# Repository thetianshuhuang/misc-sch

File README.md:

# misc-sch
Random eagle schematics, some of which have been fabricated, some that haven't, and some that probably will never get made.

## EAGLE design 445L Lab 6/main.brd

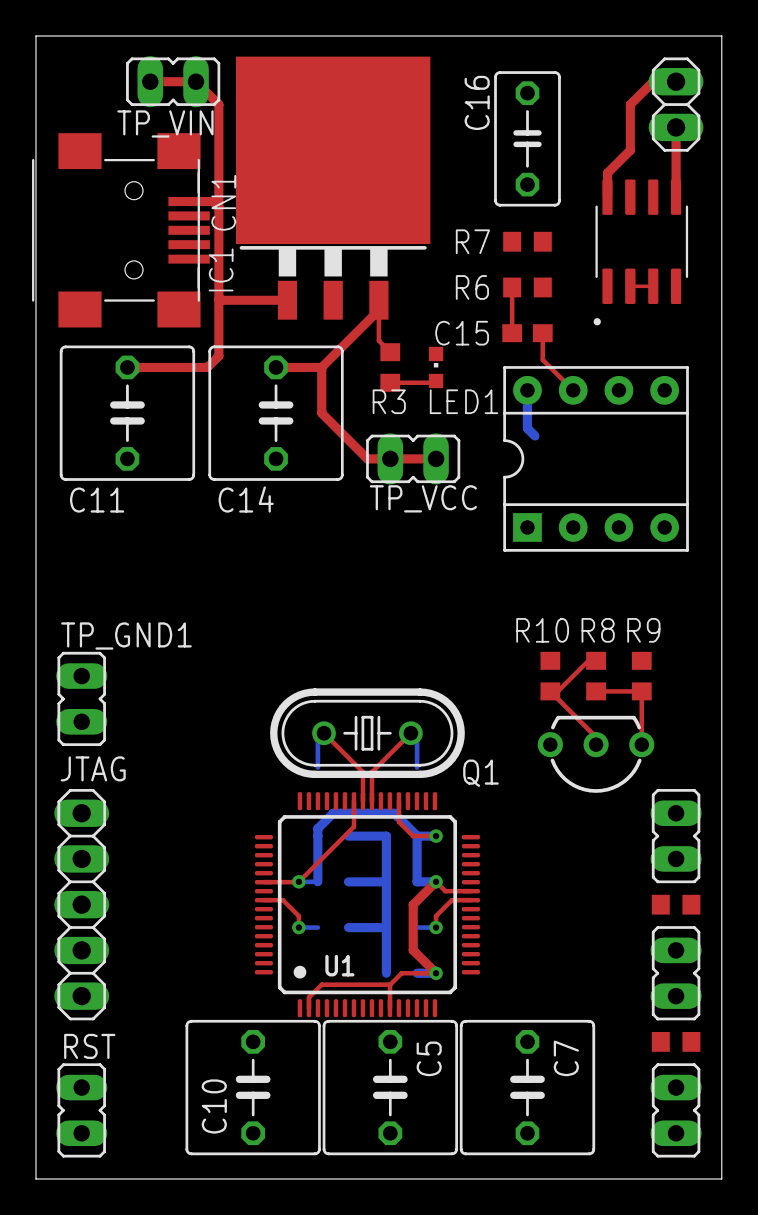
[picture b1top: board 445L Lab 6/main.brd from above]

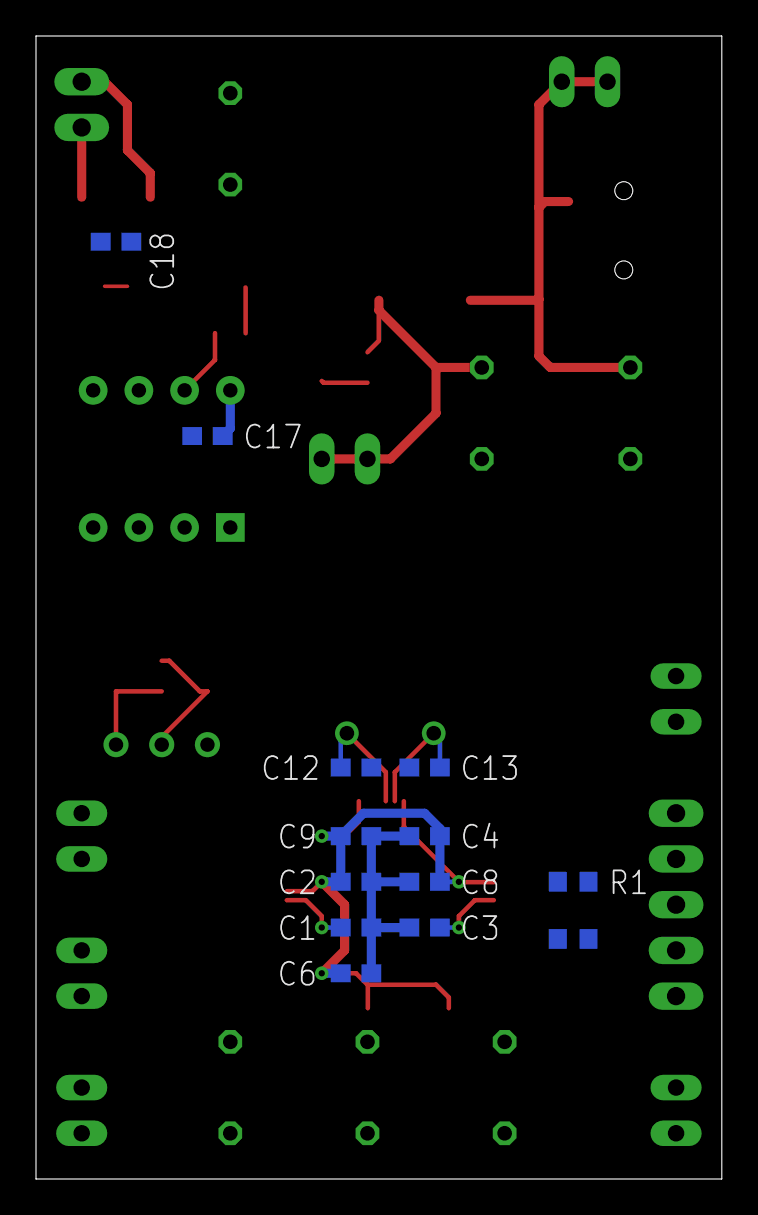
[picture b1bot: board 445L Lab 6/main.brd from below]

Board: 2 copper layers, 38.1 x 63.5 mm, 45 parts (13 on the bottom side), 26 nets.

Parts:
BTN0, BTN4: JP1
C1, C3, C8, C9, C15, C17, C18: 0.1uF; C0603
C2, C4, C6: 0.01uF; C0603
C5, C10: 1uF; C050-075X075
C7: 2.2uF; C050-075X075
C11, C14: 4.7uF; C050-075X075
C12, C13: 10pF; C0603
C16: 3.3uF; C050-035X075
CN1: USB-MINIB
IC1: LM2937; TO263-3
IC2: LM4041CILPRLP; LP_O-PBCY-W3
JTAG: 1X05
LED1: CHIPLED_0603
Q1: 16MHz; HC49U-V
R1: 1M; R0603
R2: 10K; R0603
R3: 4.7K; R0603
R4, R5, R9: 10k; R0603
R6, R7: 2.2k; R0603
R8: 47k; R0603
R10: 2k; R0603
RST: JP1
SPK: 1X02
TP_GND1, TP_GND2: JP1
TP_VCC: JP1
TP_VIN: JP1
U1: TM4C1233H6PM; LQFP64
U2: TPA731D; SOIC127P600X175-8N
U3: TLV5616; DIL08

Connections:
5V_IN: C11.1, CN1.VBUS, IC1.1, TP_VIN.1, TP_VIN.2
AMP_DC_FILTER: C15.2, R6.1
AMP_IN+: C16.1, U2.2, U2.3
AMP_IN-: R6.2, R7.1, U2.4
FSS: U1.20, U3.4
GND: BTN0.2, BTN4.2, C1.2, C2.2, C3.2, C4.2, C5.2, C6.2, C7.2, C8.2, C9.2, C10.2, C11.2, C12.2, C13.2, C14.2, C16.2, C17.2, C18.2, CN1.GND, IC1.2, IC2.3, JTAG.5, LED1.C, R9.2, RST.2, TP_GND1.1, TP_GND1.2, TP_GND2.1, TP_GND2.2, U1.3, U1.12, U1.27, U1.34, U1.35, U1.39, U1.55, U2.7, U3.3, U3.5
LED_RESIST: LED1.A, R3.1
MOSI: U1.22, U3.1
OSC0: C12.1, Q1.1, U1.40
OSC1: C13.1, Q1.2, U1.41
PF0: BTN0.1, R4.2, U1.28
PF4: BTN4.1, R5.2, U1.5
RST: R2.1, RST.1, U1.38
SCLK: U1.19, U3.2
TCK: JTAG.4, U1.52
TDI: JTAG.2, U1.50
TDO: JTAG.1, U1.49
TMS: JTAG.3, U1.51
VCC: C2.1, C4.1, C6.1, C8.1, C9.1, C10.1, C14.1, C17.1, C18.1, IC1.3, R1.2, R2.2, R3.2, R4.1, R5.1, R10.2, TP_VCC.1, TP_VCC.2, U1.2, U1.11, U1.26, U1.37, U1.42, U1.54, U2.6, U3.8
VDAC: C15.1, U3.7
VDDC: C1.1, C3.1, C5.1, C7.1, U1.25, U1.56
VO+: R7.2, SPK.1, U2.5
VO-: SPK.2, U2.8
VREF: IC2.2, R8.1, R10.1, U3.6
VREF_FEEDBACK: IC2.1, R8.2, R9.1
WAKE: R1.1, U1.32

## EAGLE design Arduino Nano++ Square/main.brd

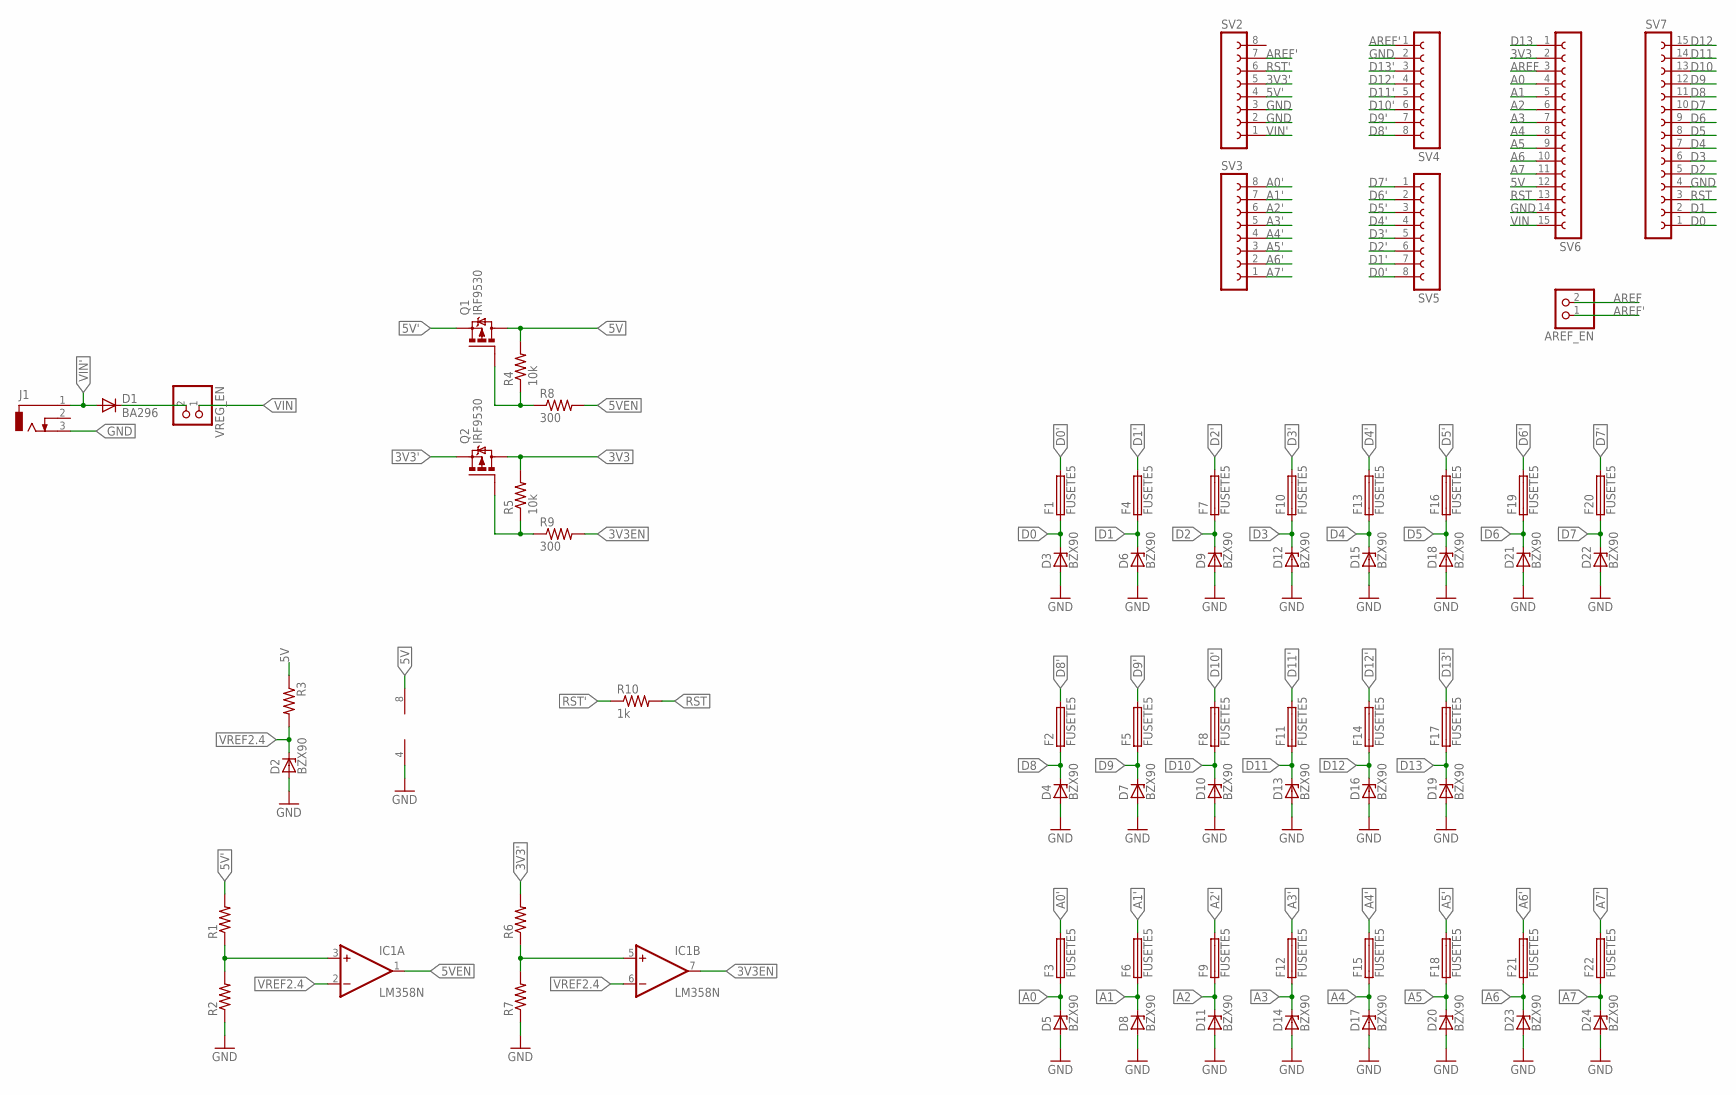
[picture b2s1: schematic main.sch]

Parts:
AREF_EN: PINHD-1X2; 1X02
D1: BA296; P2-15
D2, D3, D4, D5, D6, D7, D8, D9, D10, D11, D12, D13, D14, D15, D16, D17, D18, D19, D20, D21, D22, D23, D24: BZX90; DO34Z7
F1, F2, F3, F4, F5, F6, F7, F8, F9, F10, F11, F12, F13, F14, F15, F16, F17, F18, F19, F20, F21, F22: FUSETE5; TE5
IC1: LM358N; DIL08
J1: DCJ0303
Q1, Q2: IRF9530; TO220BV
R1, R2, R3, R6, R7: R-US_0204/7; 0204/7
R4, R5: 10k; 0204/7
R8, R9: 300; 0204/7
R10: 1k; 0204/7
SV2, SV3, SV4, SV5: FE08-1; FE08
SV6, SV7: FE15-1; FE15
VREG_EN: PINHD-1X2; 1X02

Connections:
3V3: Q2.D, R5.2, SV6.2
3V3': Q2.S, R6.2, SV2.5
3V3EN: IC1.7 (OUT), R9.2
5V: IC1.8 (V+), Q1.D, R3.1, R4.2, SV6.12
5V': Q1.S, R1.2, SV2.4
5VEN: IC1.1 (OUT), R8.2
A0: D5.C, F3.1, SV6.4
A0': F3.2, SV3.8
A1: D8.C, F6.1, SV6.5
A1': F6.2, SV3.7
A2: D11.C, F9.1, SV6.6
A2': F9.2, SV3.6
A3: D14.C, F12.1, SV6.7
A3': F12.2, SV3.5
A4: D17.C, F15.1, SV6.8
A4': F15.2, SV3.4
A5: D20.C, F18.1, SV6.9
A5': F18.2, SV3.3
A6: D23.C, F21.1, SV6.10
A6': F21.2, SV3.2
A7: D24.C, F22.1, SV6.11
A7': F22.2, SV3.1
AREF: AREF_EN.2, SV6.3
AREF': AREF_EN.1, SV2.7, SV4.1
D0: D3.C, F1.1, SV7.1
D0': F1.2, SV5.8
D1: D6.C, F4.1, SV7.2
D1': F4.2, SV5.7
D2: D9.C, F7.1, SV7.5
D2': F7.2, SV5.6
D3: D12.C, F10.1, SV7.6
D3': F10.2, SV5.5
D4: D15.C, F13.1, SV7.7
D4': F13.2, SV5.4
D5: D18.C, F16.1, SV7.8
D5': F16.2, SV5.3
D6: D21.C, F19.1, SV7.9
D6': F19.2, SV5.2
D7: D22.C, F20.1, SV7.10
D7': F20.2, SV5.1
D8: D4.C, F2.1, SV7.11
D8': F2.2, SV4.8
D9: D7.C, F5.1, SV7.12
D9': F5.2, SV4.7
D10: D10.C, F8.1, SV7.13
D10': F8.2, SV4.6
D11: D13.C, F11.1, SV7.14
D11': F11.2, SV4.5
D12: D16.C, F14.1, SV7.15
D12': F14.2, SV4.4
D13: D19.C, F17.1, SV6.1
D13': F17.2, SV4.3
GND: D2.A, D3.A, D4.A, D5.A, D6.A, D7.A, D8.A, D9.A, D10.A, D11.A, D12.A, D13.A, D14.A, D15.A, D16.A, D17.A, D18.A, D19.A, D20.A, D21.A, D22.A, D23.A, D24.A, IC1.4 (V-), J1.3, R2.1, R7.1, SV2.2, SV2.3, SV4.2, SV6.14, SV7.4
unnamed: D1.C, VREG_EN.2
unnamed: Q2.G, R5.1, R9.1
unnamed: Q1.G, R4.1, R8.1
unnamed: IC1.3 (+IN), R1.1, R2.2
unnamed: IC1.5 (+IN), R6.1, R7.2
RST: R10.2, SV6.13, SV7.3
RST': R10.1, SV2.6
VIN: SV6.15, VREG_EN.1
VIN': D1.A, J1.1, SV2.1
VREF2.4: D2.C, IC1.2 (-IN), IC1.6 (-IN), R3.2

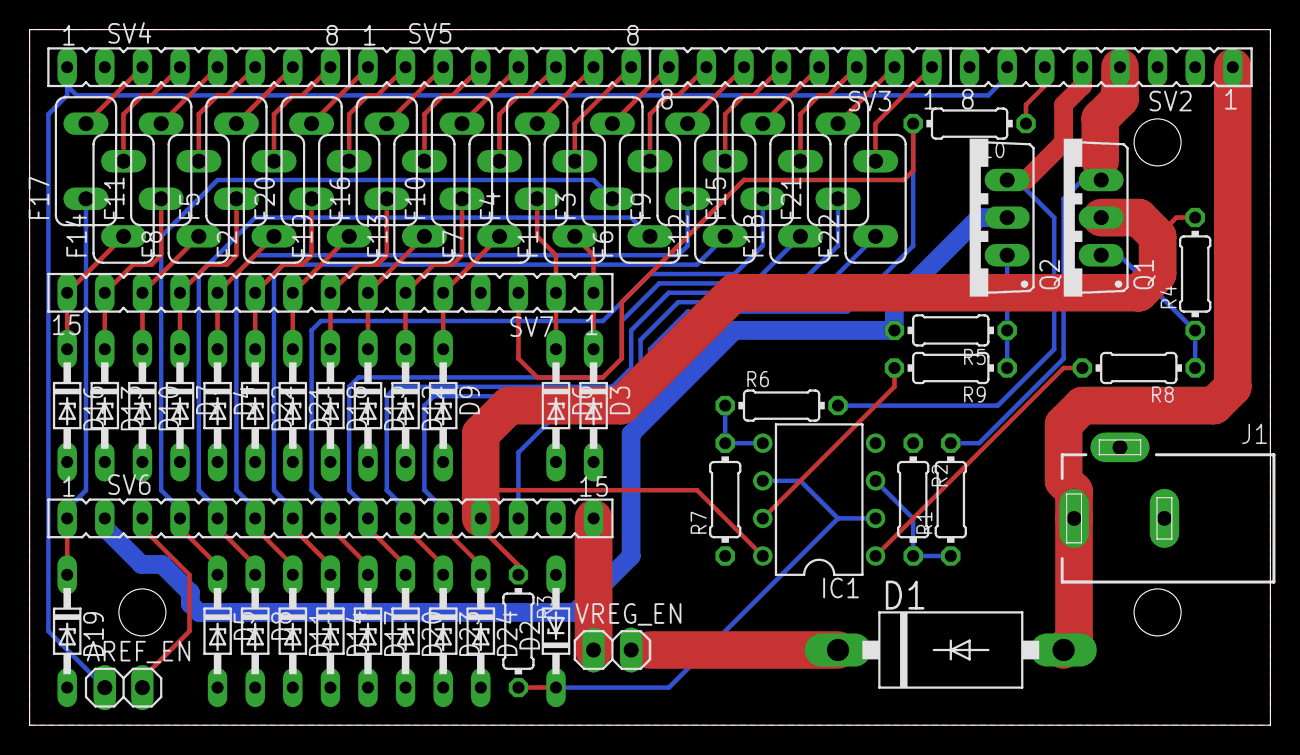
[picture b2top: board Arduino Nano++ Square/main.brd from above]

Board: 2 copper layers, 83.8 x 47.0 mm, 68 parts (0 on the bottom side), 63 nets.

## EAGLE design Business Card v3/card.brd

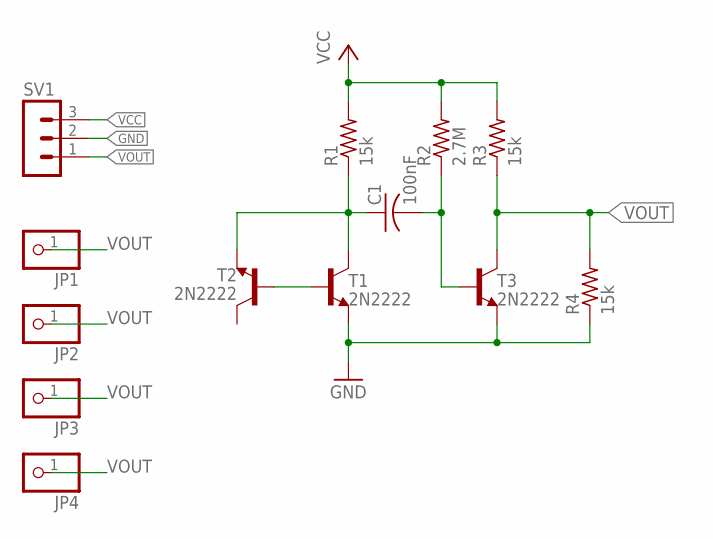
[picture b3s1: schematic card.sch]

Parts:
C1: 100nF; C025-025X050
JP1, JP2, JP3, JP4: PINHD-1X1; 1X01
R1, R3, R4: 15k; 0204/7
R2: 2.7M; 0204/7
SV1: MA03-1
T1, T2, T3: 2N2222; TO18

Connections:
GND: R4.1, SV1.2, T1.1 (E), T3.1 (E)
unnamed: T1.2 (B), T2.2 (B)
unnamed: C1.1, R1.1, T1.3 (C), T2.1 (E)
unnamed: C1.2, R2.1, T3.2 (B)
VCC: R1.2, R2.2, R3.2, SV1.3
VOUT: JP1.1, JP2.1, JP3.1, JP4.1, R3.1, R4.2, SV1.1, T3.3 (C)

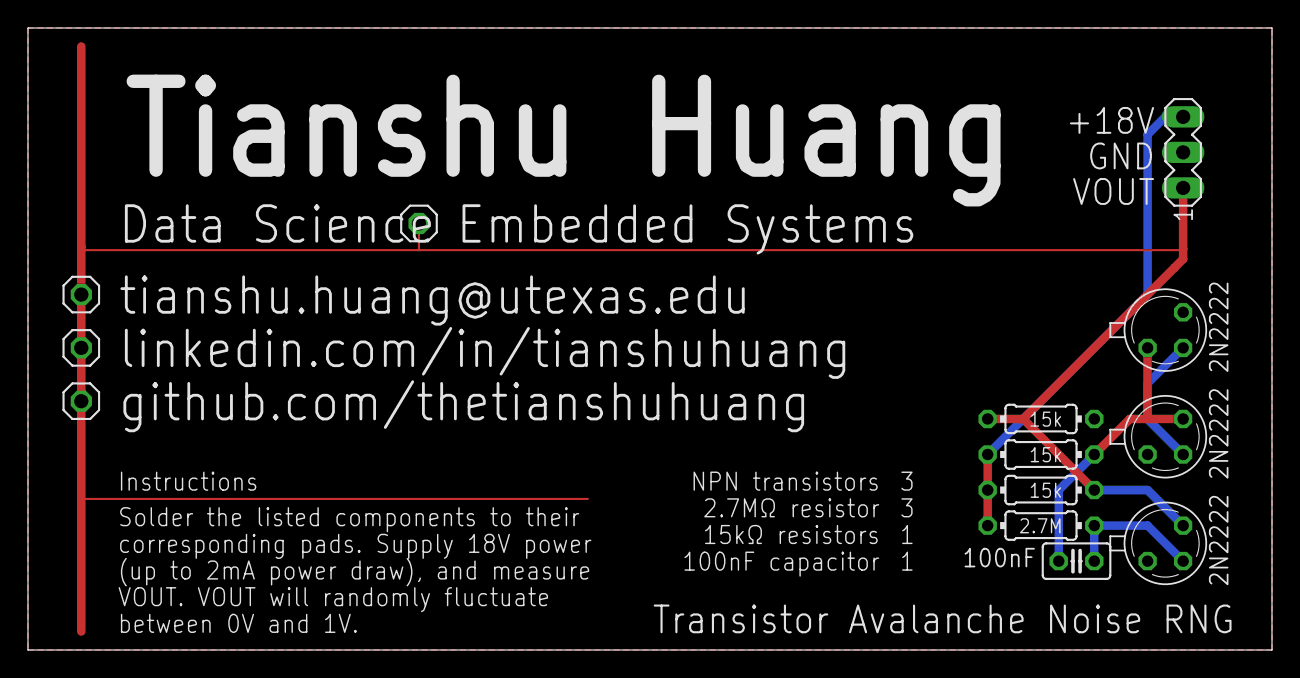
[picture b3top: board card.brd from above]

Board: 2 copper layers, 88.9 x 44.5 mm, 13 parts (0 on the bottom side), 6 nets.

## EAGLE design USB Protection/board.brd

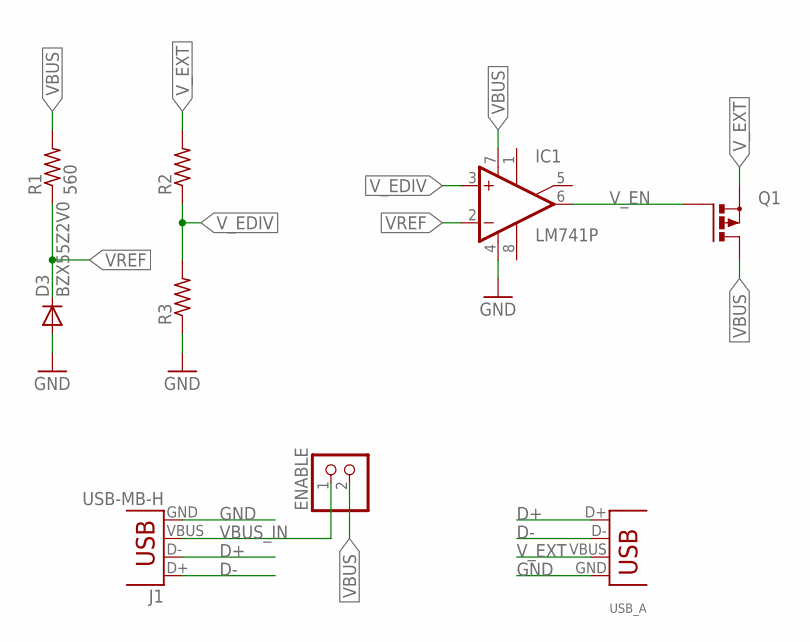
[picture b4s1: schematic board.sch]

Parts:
D3: BZX55Z2V0; DO35-7
ENABLE: PINHD-1X2; 1X02
IC1: LM741P; DIL08
J1: USB-MB-H
Q1: PMOSFET_PTO220BV; TO220BV
R1: 560; 0207/7
R2, R3: R-US_0207/7; 0207/7
USB_A: USB-A-H

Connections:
D+: J1.D-, USB_A.D+
D-: J1.D+, USB_A.D-
GND: D3.A, IC1.4 (V-), J1.GND, R3.1, USB_A.GND
VBUS: ENABLE.2, IC1.7 (V+), Q1.D, R1.2
VBUS_IN: ENABLE.1, J1.VBUS
VREF: D3.C, IC1.2 (-IN), R1.1
V_EDIV: IC1.3 (+IN), R2.1, R3.2
V_EN: IC1.6 (OUT), Q1.G
V_EXT: Q1.S, R2.2, USB_A.VBUS

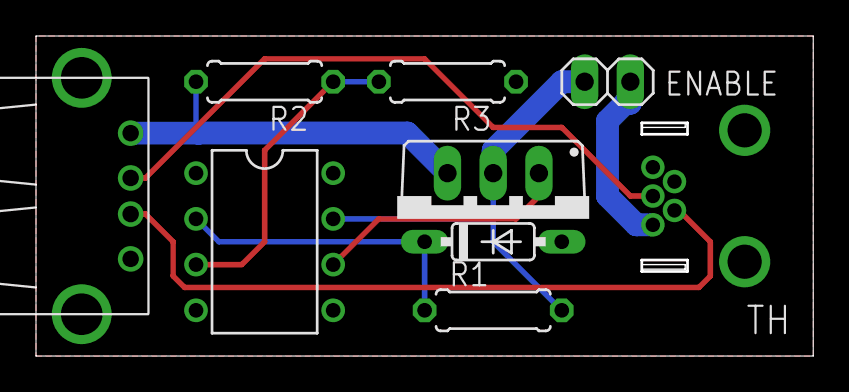
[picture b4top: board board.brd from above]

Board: 2 copper layers, 43.0 x 17.6 mm, 9 parts (0 on the bottom side), 9 nets.

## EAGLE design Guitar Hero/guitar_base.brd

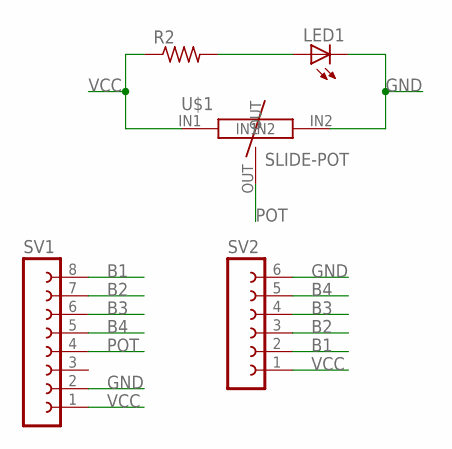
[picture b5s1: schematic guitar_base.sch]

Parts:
LED1: LED5MM
R2: R-US_0207/7; 0207/7
SV1: FE08-1; FE08
SV2: FE06-1; FE06
U$1: SLIDE-POT

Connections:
B1: SV1.8, SV2.2
B2: SV1.7, SV2.3
B3: SV1.6, SV2.4
B4: SV1.5, SV2.5
GND: LED1.K (C), SV1.2, SV2.6, U$1.IN2
unnamed: LED1.A, R2.2
POT: SV1.4, U$1.OUT
VCC: R2.1, SV1.1, SV2.1, U$1.IN1

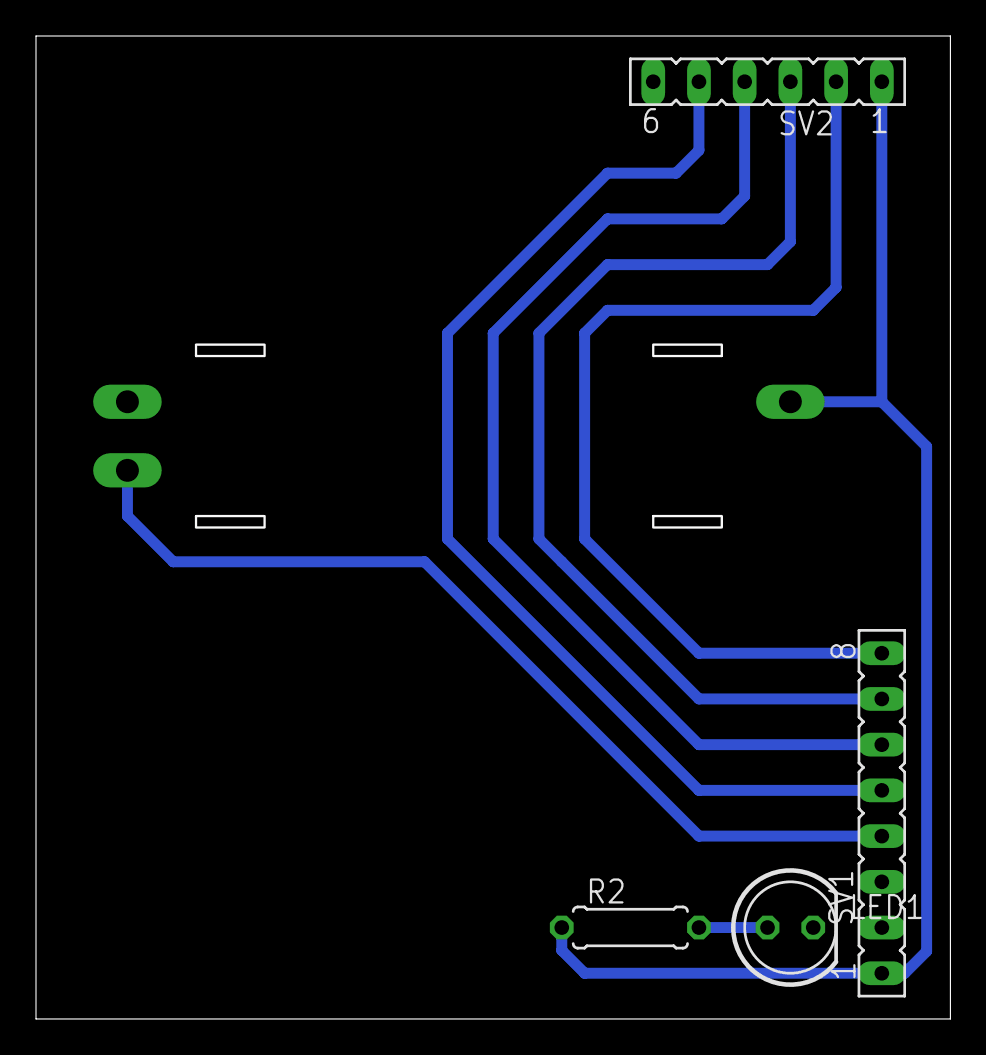
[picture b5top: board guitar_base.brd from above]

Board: 2 copper layers, 50.7 x 54.5 mm, 5 parts (0 on the bottom side), 8 nets.

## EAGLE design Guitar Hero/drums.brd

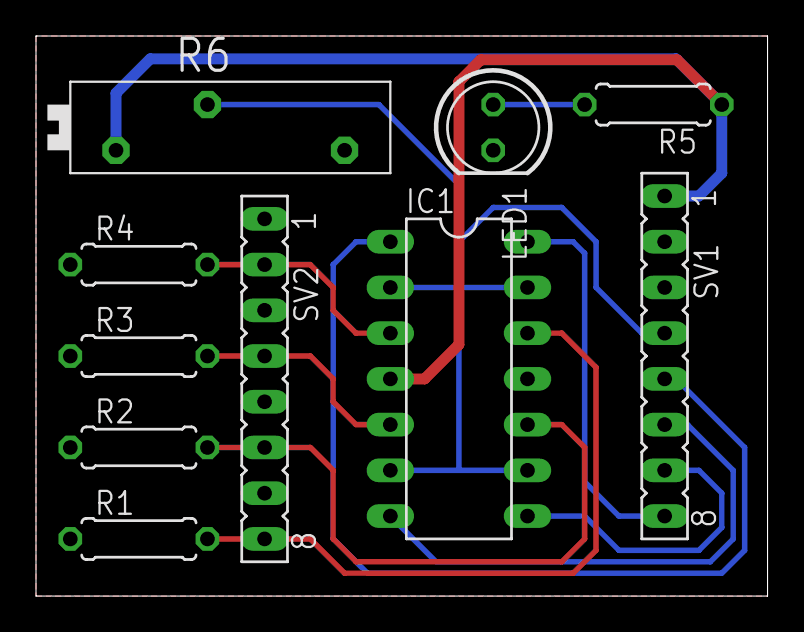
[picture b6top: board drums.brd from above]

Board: 2 copper layers, 40.6 x 31.1 mm, 10 parts (0 on the bottom side), 12 nets.

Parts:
IC1: ICL7641P; DIL14
LED1: LED5MM
R1, R2, R3, R4, R5: 0207/7
R6: PT-SPIN
SV1, SV2: FE08

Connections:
B1: IC1.1, SV1.5
B2: IC1.7, SV1.6
B3: IC1.8, SV1.7
B4: IC1.14, SV1.8
D1: IC1.3, R4.2, SV2.2
D2: IC1.5, R3.2, SV2.4
D3: IC1.10, R2.2, SV2.6
D4: IC1.12, R1.2, SV2.8
GND: IC1.11, LED1.K, R1.1, R2.1, R3.1, R4.1, R6.2, SV1.2, SV2.1, SV2.3, SV2.5, SV2.7
unnamed: LED1.A, R5.2
VCC: IC1.4, R5.1, R6.1, SV1.1
VREF: IC1.2, IC1.6, IC1.9, IC1.13, R6.3, SV1.4

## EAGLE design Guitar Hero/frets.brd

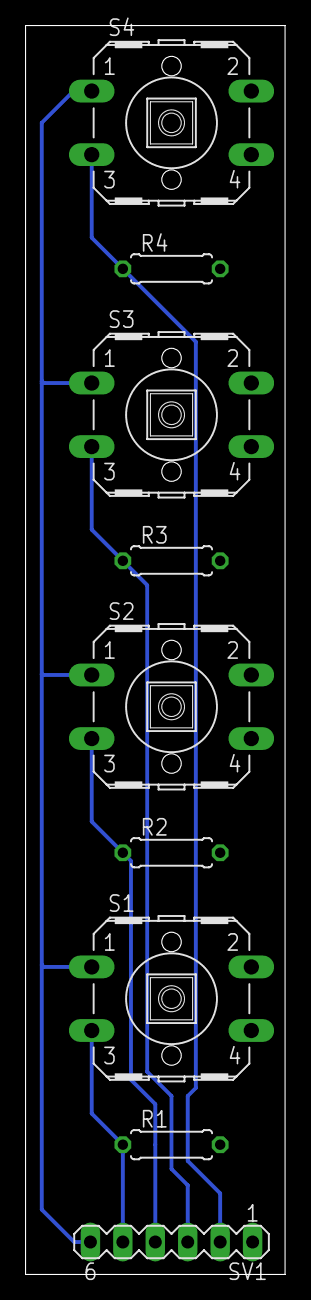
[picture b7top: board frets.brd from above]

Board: 2 copper layers, 20.3 x 97.8 mm, 9 parts (0 on the bottom side), 6 nets.

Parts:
R1, R2, R3, R4: 10k; 0207/7
S1, S2, S3, S4: RACON12
SV1: MA06-1

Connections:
B1: R1.1, S1.3, SV1.5
B2: R2.1, S2.3, SV1.4
B3: R3.1, S3.3, SV1.3
B4: R4.1, S4.3, SV1.2
GND: R1.2, R2.2, R3.2, R4.2, SV1.1
VCC: S1.1, S2.1, S3.1, S4.1, SV1.6

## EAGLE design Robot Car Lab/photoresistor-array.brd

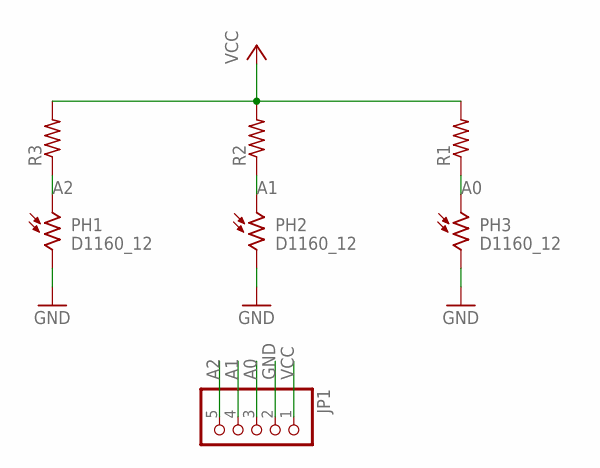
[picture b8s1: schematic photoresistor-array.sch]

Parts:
JP1: PINHD-1X5; 1X05
PH1, PH2, PH3: D1160_12; D11XX
R1, R2, R3: R-US_0207/10; 0207/10

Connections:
A0: JP1.3, PH3.1, R1.1
A1: JP1.4, PH2.1, R2.1
A2: JP1.5, PH1.1, R3.1
GND: JP1.2, PH1.2, PH2.2, PH3.2
VCC: JP1.1, R1.2, R2.2, R3.2

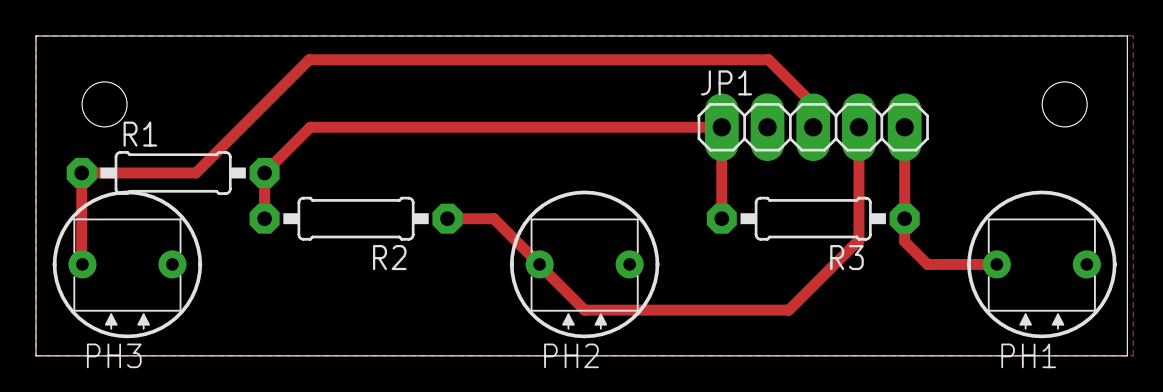
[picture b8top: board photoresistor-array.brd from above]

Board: 2 copper layers, 60.6 x 17.8 mm, 7 parts (0 on the bottom side), 5 nets.

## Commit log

2018-03-25 Updated casemod circuit, added a few images
2018-03-26 Added images for casemod PCB
2018-04-03 Added USB protection circuit
2018-04-03 Removed power zener diode
2018-04-08 Created schematic for three phase motor as encoder op amp circuit
2018-04-13 Changed to USB port based connection
2018-04-17 Started on base board; made board layout for peripherals
2018-04-17 Added drums, photoresistor array
2018-04-17 Added drill holes to butotn mounts
2018-04-18 Widened power traces
2018-04-19 Added guitar base
2018-04-22 Nano++ Concept
2018-04-23 Nano++ schematic; guitar hero redo to not use 1/64th bit
2018-04-23 Made version 2 of Nano++
2018-04-23 Increased vreg clearance
2018-04-24 Removed vreg slot
2018-06-16 Added redo of nano++ (no longer conforms to arduino format)
2020-03-04 Added lab 6
2020-03-09 Finished layout
2020-03-09 Added lbr for dip-8
2020-03-09 Misc updates to lab 6

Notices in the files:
parts and their libraries:
ti-tiva: Copyright (C) 2013, Bob Starr
SparkFun-Retired: Licensing: Creative Commons ShareAlike 4.0 International - https://creativecommons.org/licenses/by-sa/4.0
